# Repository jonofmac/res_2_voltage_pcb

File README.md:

# res_2_voltage_pcb
PCB Design for my resistance to voltage converter board

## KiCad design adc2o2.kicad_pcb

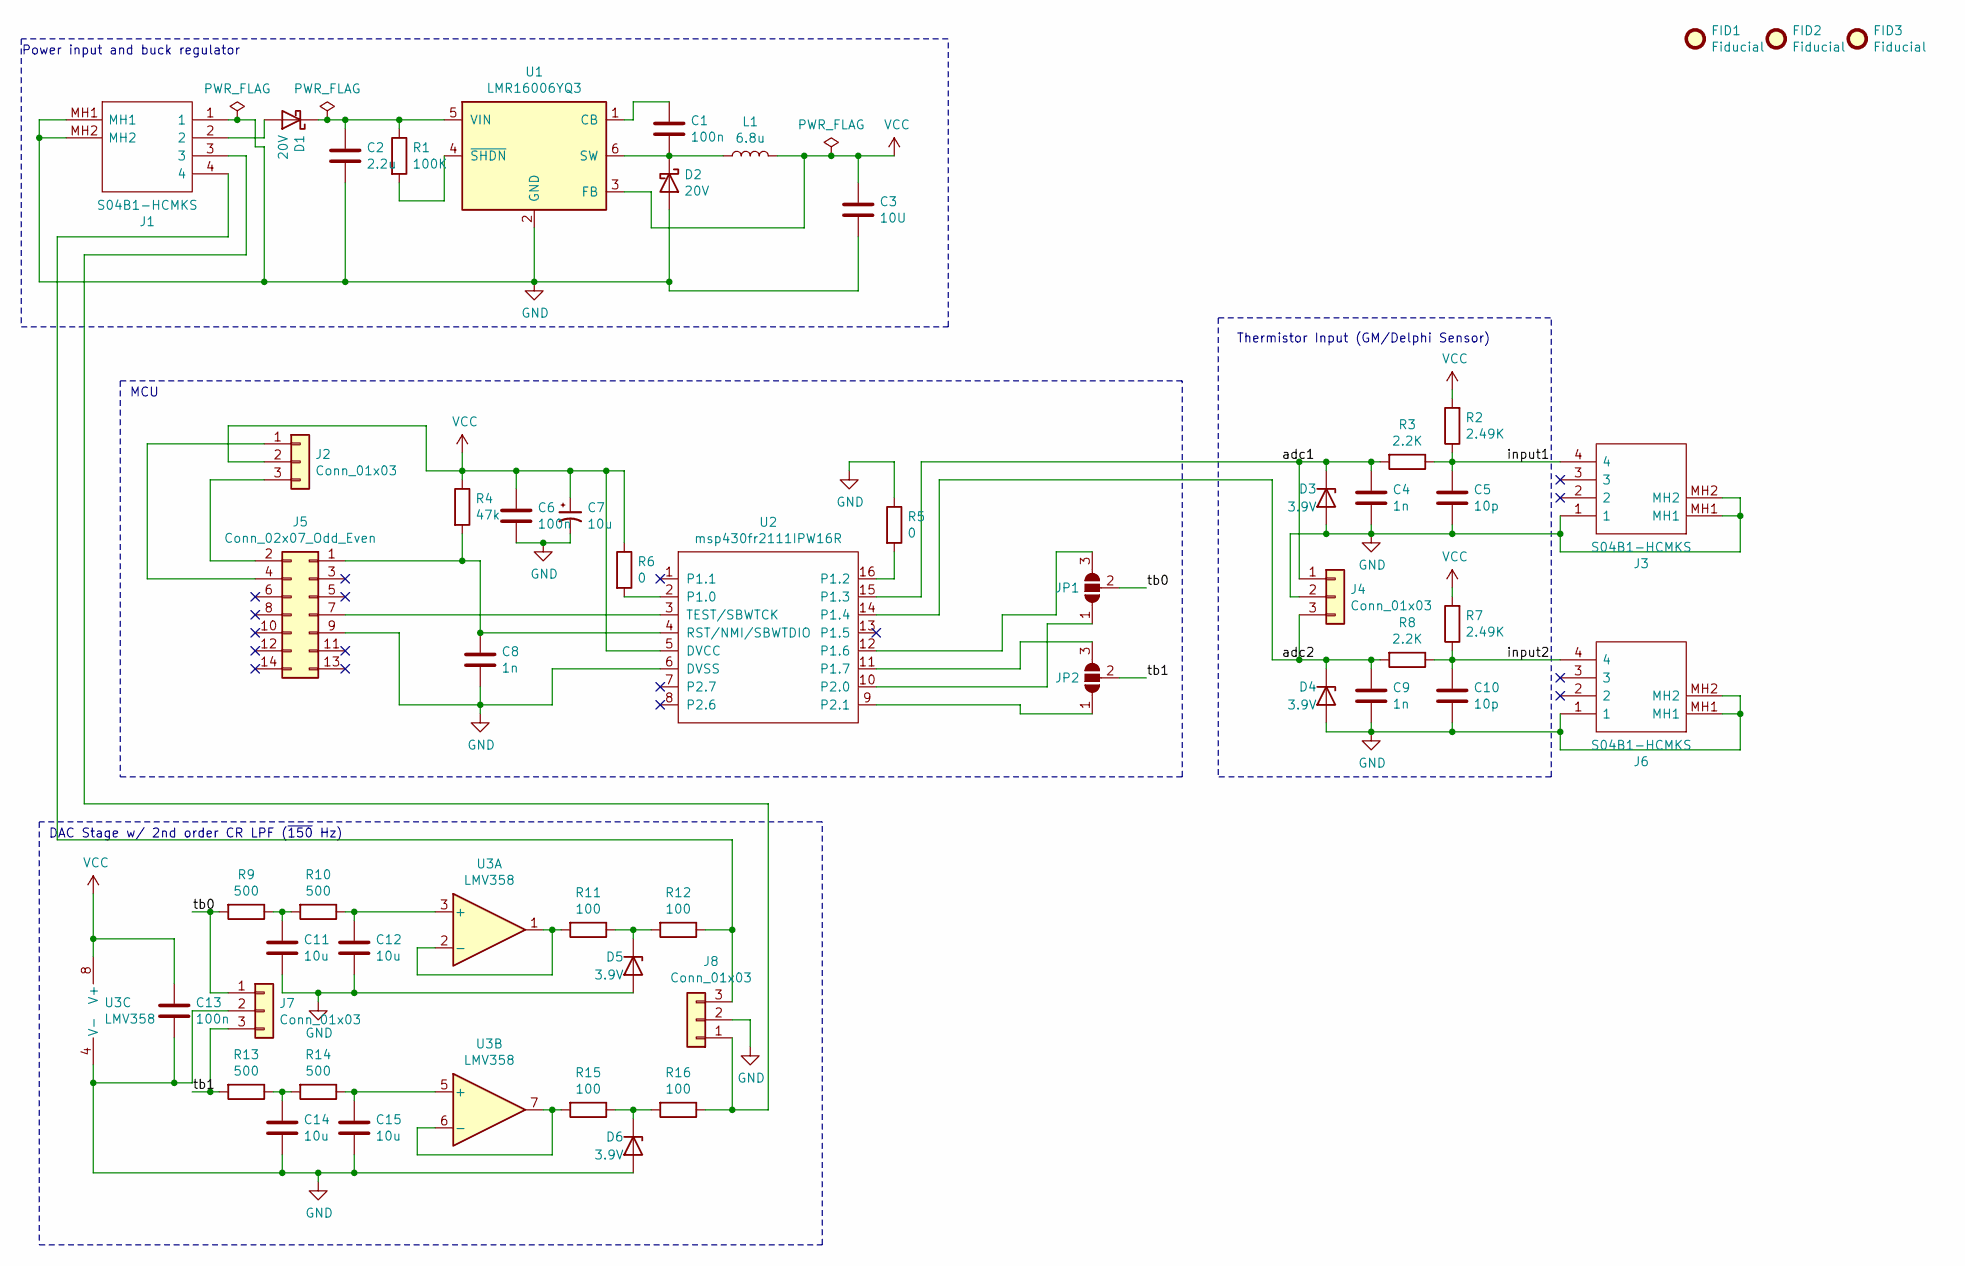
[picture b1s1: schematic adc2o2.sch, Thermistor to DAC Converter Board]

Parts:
C1, C13: 100n; C_0603_1608Metric
C2: 2.2u; R_0603_1608Metric
C3: 10U; C_0603_1608Metric
C4, C8, C9: 1n; C_0603_1608Metric
C5, C10: 10p; C_0603_1608Metric
C6: 100n; C_0805_2012Metric
C7: 10u; C_0603_1608Metric
C11, C12, C14, C15: 10u; C_0805_2012Metric
D1: 20V; D_0603_1608Metric; Mouser Part Number 750-CDBU0520
D2: 20V; D_0603_1608Metric
D3, D4, D5, D6: 3.9V; D_0603_1608Metric
FID1, FID2, FID3: Fiducial; Fiducial_1mm_Mask2mm
J1, J3, J6: S04B1-HCMKS; S04B1HCMKS; Mouser Part Number 306-S04B1-HCMKS
J2, J4, J7, J8: Conn_01x03; PinHeader_1x03_P2.54mm_Vertical
J5: Conn_02x07_Odd_Even; PinHeader_2x07_P2.54mm_Vertical
JP1, JP2: SolderJumper_3_Open; SolderJumper-3_P1.3mm_Open_RoundedPad1.0x1.5mm
L1: 6.8u; L_1210_3225Metric
R1: 100K; R_0603_1608Metric; Mouser Part Number 279-CRG0603F100K
R2, R7: 2.49K; R_0603_1608Metric
R3, R8: 2.2K; R_0603_1608Metric
R4: 47k; R_0603_1608Metric
R5, R6: 0; R_0603_1608Metric
R9, R10, R13, R14: 500; R_0603_1608Metric
R11, R12, R15, R16: 100; R_0603_1608Metric
U1: LMR16006YQ3; SOT-23-6
U2: msp430fr2111IPW16R; SOIC-16
U3: LMV358; TSSOP-8_4.4x3mm_P0.65mm

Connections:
/adc1: C4.1, D3.1 (K), J4.1, R3.2, U2.15 (P1.3)
/adc2: C9.1, D4.1 (K), J4.3, R8.2, U2.14 (P1.4)
/input1: C5.1, J3.4, R2.1, R3.1
/input2: C10.1, J6.4, R7.1, R8.1
/tb0: J7.1, JP1.2 (C), R9.2
/tb1: J7.3, JP2.2 (C), R13.2
GND: C2.2, C3.2, C4.2, C5.2, C6.2, C7.2, C8.2, C9.2, C10.2, C11.1, C12.1, C13.2, C14.1, C15.1, D2.2 (A), D3.2 (A), D4.2 (A), D5.2 (A), D6.2 (A), J1.1, J1.MH1, J1.MH2, J3.1, J3.MH1, J3.MH2, J4.2, J5.9, J6.1, J6.MH1, J6.MH2, J7.2, J8.2, R5.1, U1.2 (GND), U2.6 (DVSS), U3.4 (V-)
unnamed: C1.1, U1.1 (CB)
unnamed: C1.2, D2.1 (K), L1.1, U1.6 (SW)
unnamed: C2.1, D1.1 (K), R1.1, U1.5 (VIN)
unnamed: C8.1, J5.1, R4.2, U2.4 (RST/NMI/SBWTDIO)
unnamed: C11.2, R9.1, R10.2
unnamed: C12.2, R10.1, U3.3 (+)
unnamed: C14.2, R13.1, R14.2
unnamed: C15.2, R14.1, U3.5 (+)
unnamed: D1.2 (A), J1.2
unnamed: D5.1 (K), R11.1, R12.2
unnamed: D6.1 (K), R15.1, R16.2
unnamed: J1.3, J8.1, R16.1
unnamed: J1.4, J8.3, R12.1
unnamed: J2.1, J5.4
unnamed: J2.3, J5.2
unnamed: J5.7, U2.3 (TEST/SBWTCK)
unnamed: JP1.1 (A), U2.10 (P2.0)
unnamed: JP1.3 (B), U2.12 (P1.6)
unnamed: JP2.1 (A), U2.9 (P2.1)
unnamed: JP2.3 (B), U2.11 (P1.7)
unnamed: R1.2, U1.4 (~SHDN)
unnamed: R5.2, U2.16 (P1.2)
unnamed: R6.2, U2.2 (P1.0)
unnamed: R11.2, U3.1, U3.2 (-)
unnamed: R15.2, U3.6 (-), U3.7
VCC: C3.1, C6.1, C7.1, C13.1, J2.2, L1.2, R2.2, R4.1, R6.1, R7.2, U1.3 (FB), U2.5 (DVCC), U3.8 (V+)

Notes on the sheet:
Thermistor Input (GM/Delphi Sensor)
DAC Stage w/ 2nd order CR LPF (~150 Hz)
MCU
Power input and buck regulator

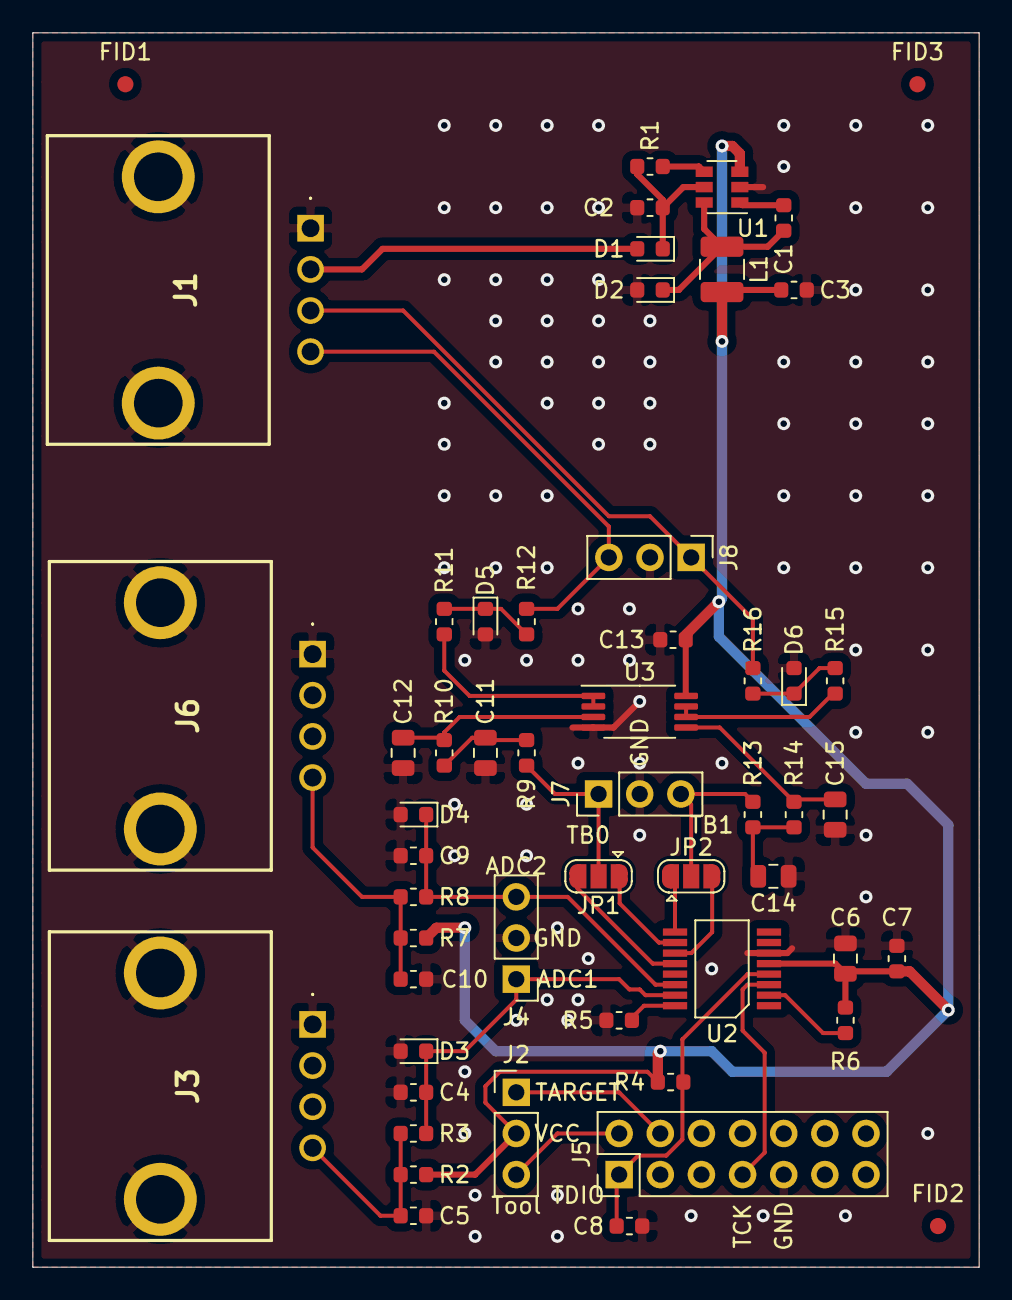
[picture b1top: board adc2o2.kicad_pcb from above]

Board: 2 copper layers, 58.4 x 76.2 mm, 54 parts (0 on the bottom side), 33 nets.
